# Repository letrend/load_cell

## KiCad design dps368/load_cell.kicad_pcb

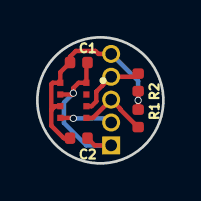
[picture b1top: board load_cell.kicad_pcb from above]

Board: 2 copper layers, 7.0 x 7.0 mm, 6 parts (1 on the bottom side), 5 nets.

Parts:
C1, C2: 100n; C_0402_1005Metric
J1: Conn_01x05_Female; PinHeader_1x05_P1.27mm_Vertical
R1, R2: 10k; R_0402_1005Metric
U1: DPS368XTSA1; XDCR_DPS368XTSA1

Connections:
+3V3: C1.2, C2.2, J1.5, R1.1, R2.1, U1.6, U1.8
/sck: J1.3, R1.2, U1.4
/sdi: J1.4, R2.2, U1.3
/sdo: J1.2, U1.5
GND: C1.1, C2.1, J1.1, U1.1, U1.7

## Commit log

2020-02-27 dps368 panel
2020-03-25 panel
2020-04-13 goddamn it
2020-05-19 with hx711 load cell publisher
2020-05-19 with calibrated value
2020-10-30 7mm diameter sensor
